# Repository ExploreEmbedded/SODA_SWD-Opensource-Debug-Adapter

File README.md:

# SODA_SWD-Opensource-Debug-Adapter
SODA is cmsis Debug Adapter based on LPC11u35.

## References and Credits</br>
<ul>
<li>[OSHChip_CMSIS_DAP_V1.0_Product](http://oshchip.org/products/OSHChip_CMSIS_DAP_V1.0_Product)</li>
<li>[mbed HDK](https://developer.mbed.org/teams/mbed/code/mbed-HDK/)</li>
<li>[mbed CMSIS DAP](https://github.com/mbedmicro/CMSIS-DAP)</li>
</ul>

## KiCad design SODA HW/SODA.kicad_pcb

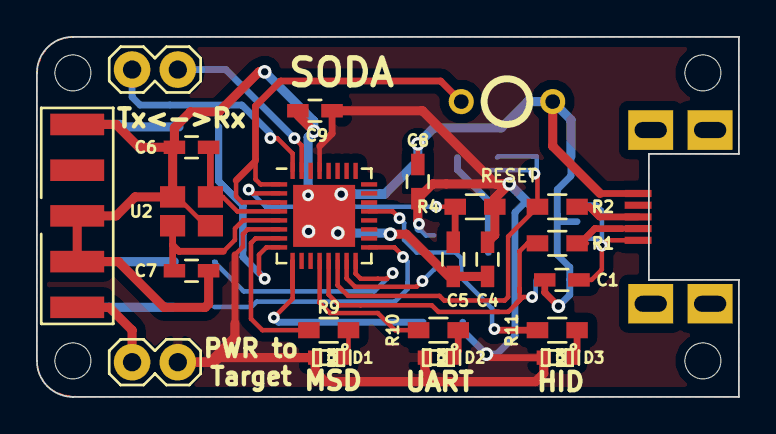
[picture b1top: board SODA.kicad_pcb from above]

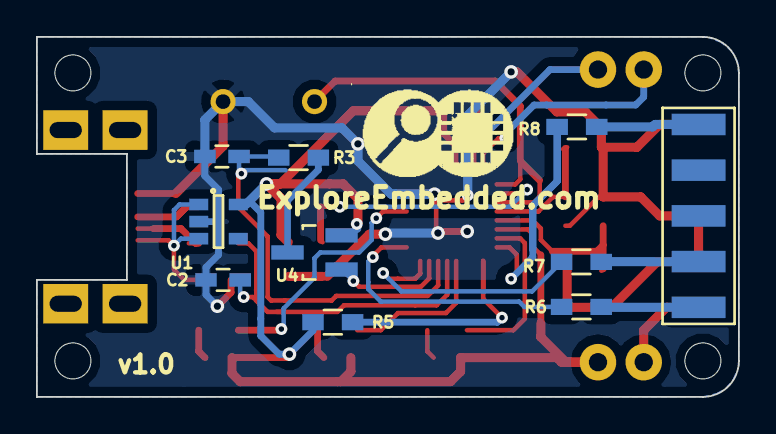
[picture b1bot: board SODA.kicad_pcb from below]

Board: 2 copper layers, 39.0 x 20.0 mm, 37 parts (10 on the bottom side), 29 nets.

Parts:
C1: 1uF,6.3V; C_0603_HandSoldering
C2, C3, C6, C7: 18pF; C_0603_HandSoldering
C4: 10uF,6.3V; C_0603_HandSoldering
C5, C8, C9: 0.1uF; C_0603_HandSoldering
CON1: USB-MICRO-B; USB_Micro-B_SMD_NEW
D1, D2, D3: LED; LED-0603_NEW
JP1: Power To Target; Pin_Header_Straight_1x02
JP2: Serial Link To Host; Pin_Header_Straight_1x02
P1: CONN_02X05; 5X2_FRC_2SIDE_EE
P2, P3, P4, P5: CONN_01X01; M3_mounting
P6: CONN_01X01; LOGO (2)
R1, R2: 33R; R_0603_HandSoldering
R3: 1.5K; R_0603_HandSoldering
R4, R5: 10K; R_0603_HandSoldering
R6, R7, R8, R9, R10, R11: 470R; R_0603_HandSoldering
SW1: SW_PUSH; SW_PUSH_SMALL_2pin_3D_xl
U1: TC1014-3.3V; SOT-23-5
U2: 12Mhz_SMD; 12Mhz_SMD_4pin
U3: LPC11U35FHI33/501; QFN-32-1EP_5x5mm_Pitch0.5mm
U4: BSS84_SOT-23; SOT-23_Handsoldering

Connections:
+3.3VP: C4.2, C8.2, C9.2, D1.1, D2.1, D3.1, JP1.1, R4.2, R5.1, U1.5, U3.6, U3.29, U4.2
GND: C1.1, C2.1, C3.1, C4.1, C5.1, C6.2, C7.2, C8.1, C9.1, CON1.5, P1.3, P1.5, P1.9, SW1.1, U1.2, U2.2, U2.4, U3.33
IF_RESET: C5.2, R4.1, U3.2
LED_HID: R10.2, U3.12
LED_MSD: R9.2, U3.7
LED_UART: R11.2, U3.21
unnamed: C6.1, U2.3, U3.4
unnamed: C7.1, U2.1, U3.5
unnamed: CON1.2, R1.2
unnamed: CON1.3, R2.2
unnamed: D1.2, R9.1
unnamed: D2.2, R10.1
unnamed: D3.2, R11.1
unnamed: JP1.2, P1.1
unnamed: P1.2, R6.2
unnamed: P1.4, R7.2
unnamed: P1.10, R8.2
unnamed: R3.2, U4.3
RESET: SW1.2, U3.1, U3.3
RX_IN: JP2.2, U3.31
TGT_NRESET: R8.1, U3.8
TGT_SWCLK: R7.1, U3.16
TGT_SWDIO: R6.1, U3.17
TX_OUT: JP2.1, U3.32
USB_CONN: U3.15, U4.1
USB_D+: C3.2, R2.1, R3.1, U3.14
USB_D-: C2.2, R1.1, U3.13
VBUS_Sense: R5.2, U3.9
V_BUS: C1.2, CON1.1, U1.1, U1.3

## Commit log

2016-05-10 Updated HW design files
2016-05-10 image url
2016-05-10 added references and credits
2016-05-10 bullets
2016-05-14 Updated firmware
    VID PID needs to obtained and changed.
2016-09-21 BOM generated
2016-11-07 bin file for LPC1768
2016-12-05 Board name modified and gerber file generated
2016-12-05 Footprint modified for 10 pin box header
